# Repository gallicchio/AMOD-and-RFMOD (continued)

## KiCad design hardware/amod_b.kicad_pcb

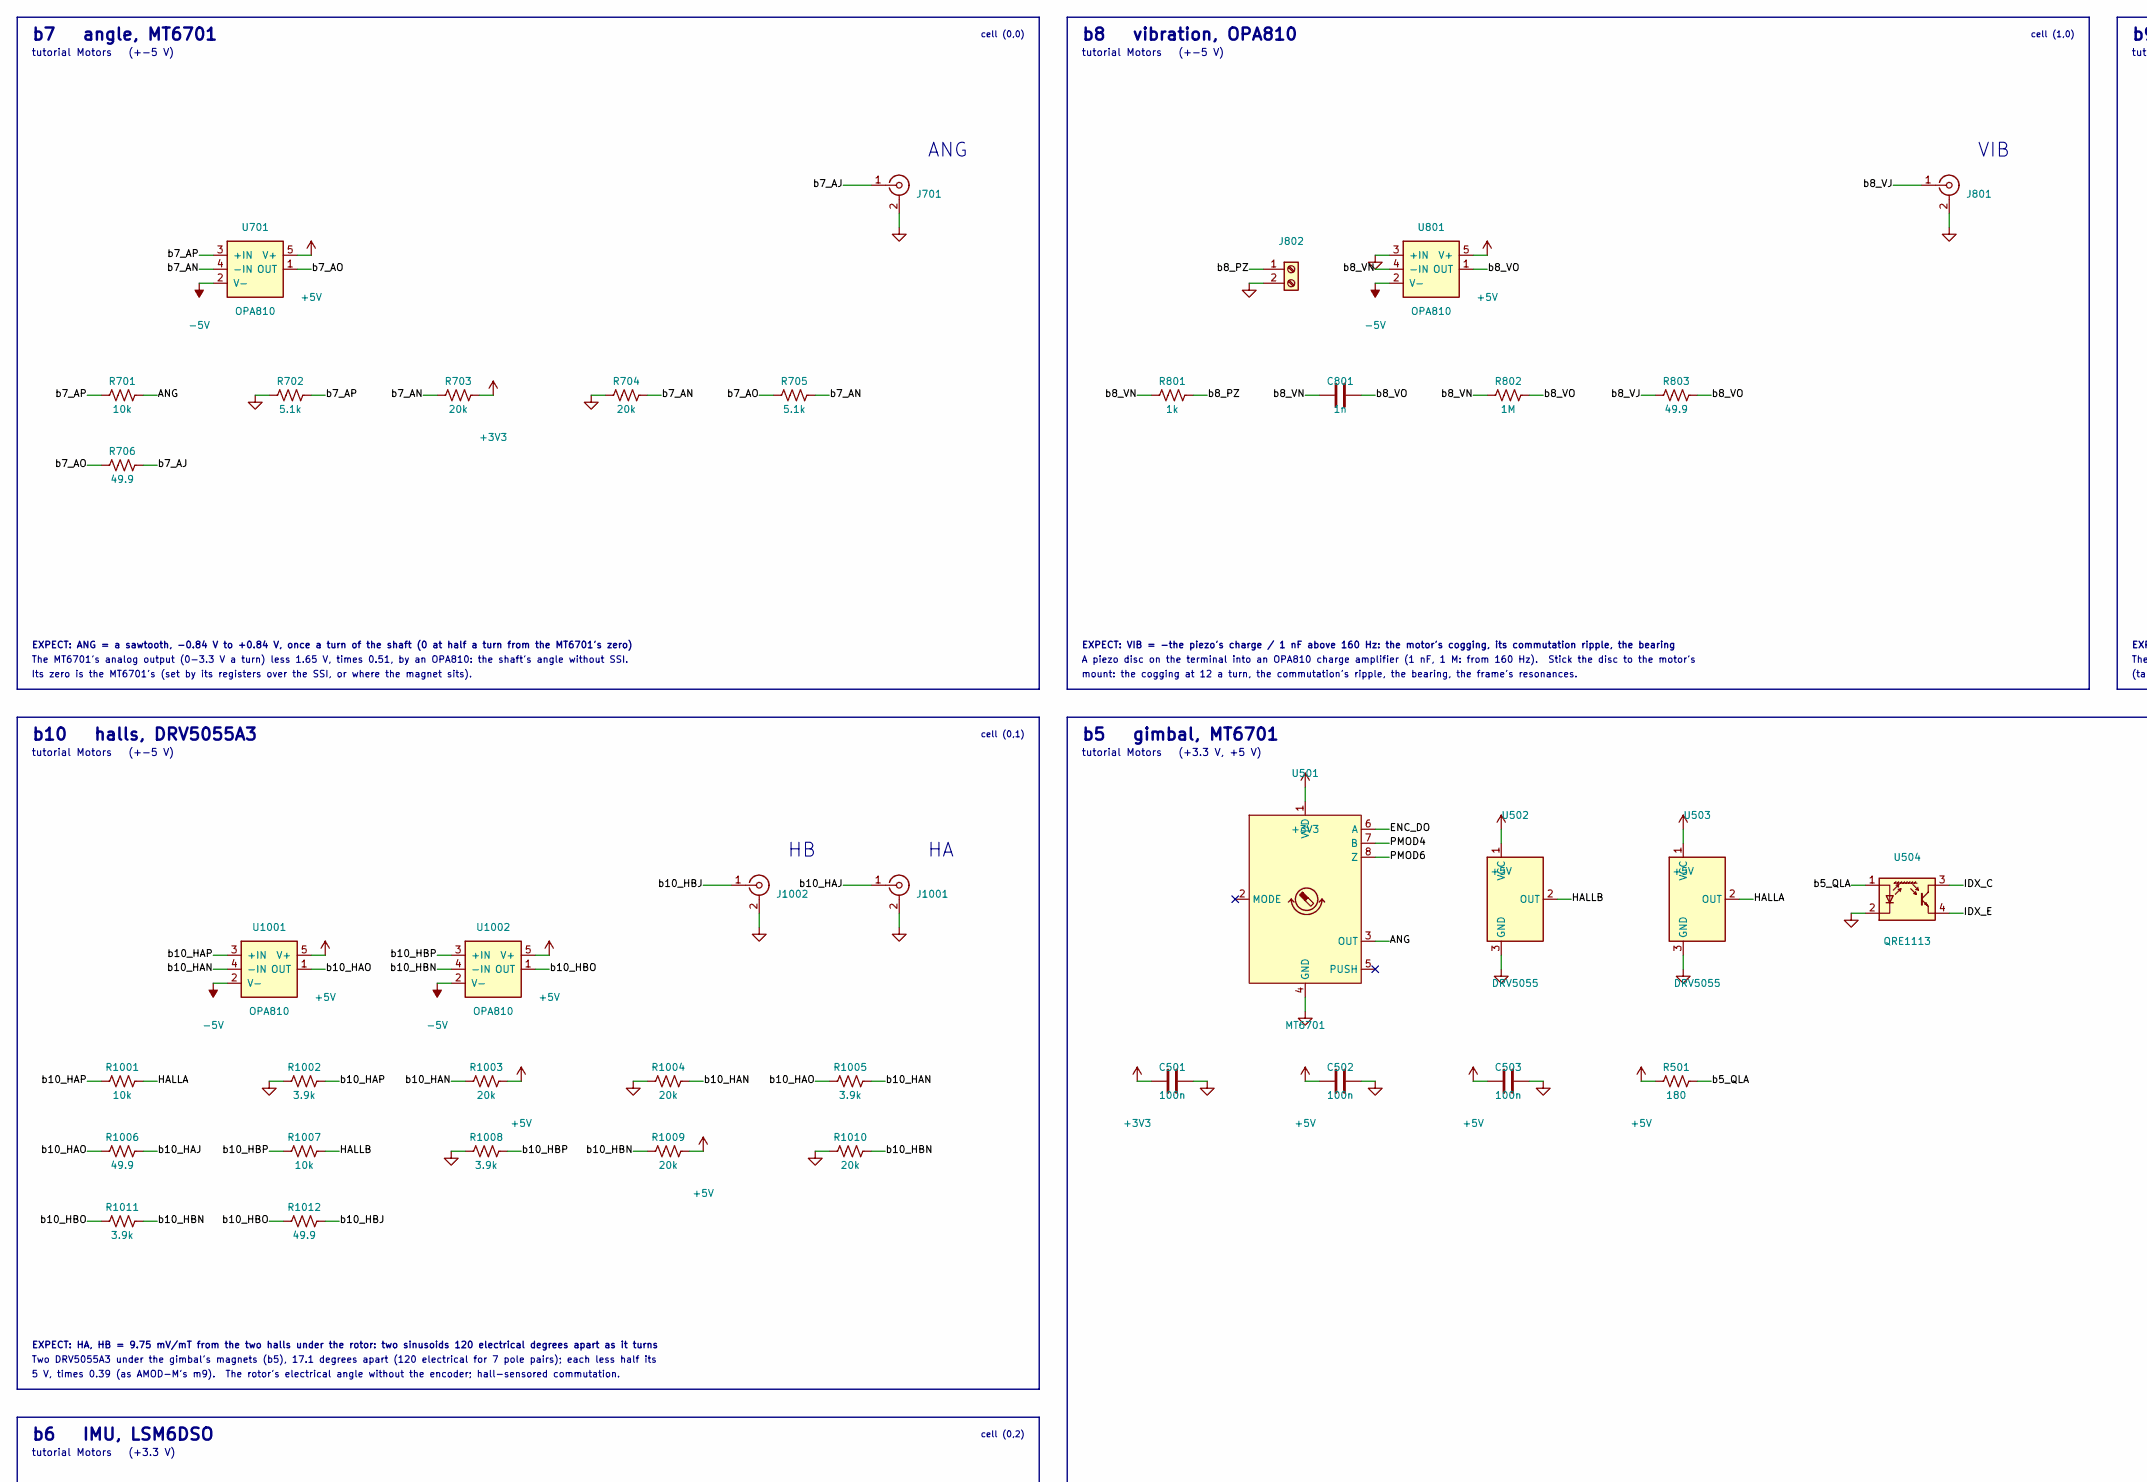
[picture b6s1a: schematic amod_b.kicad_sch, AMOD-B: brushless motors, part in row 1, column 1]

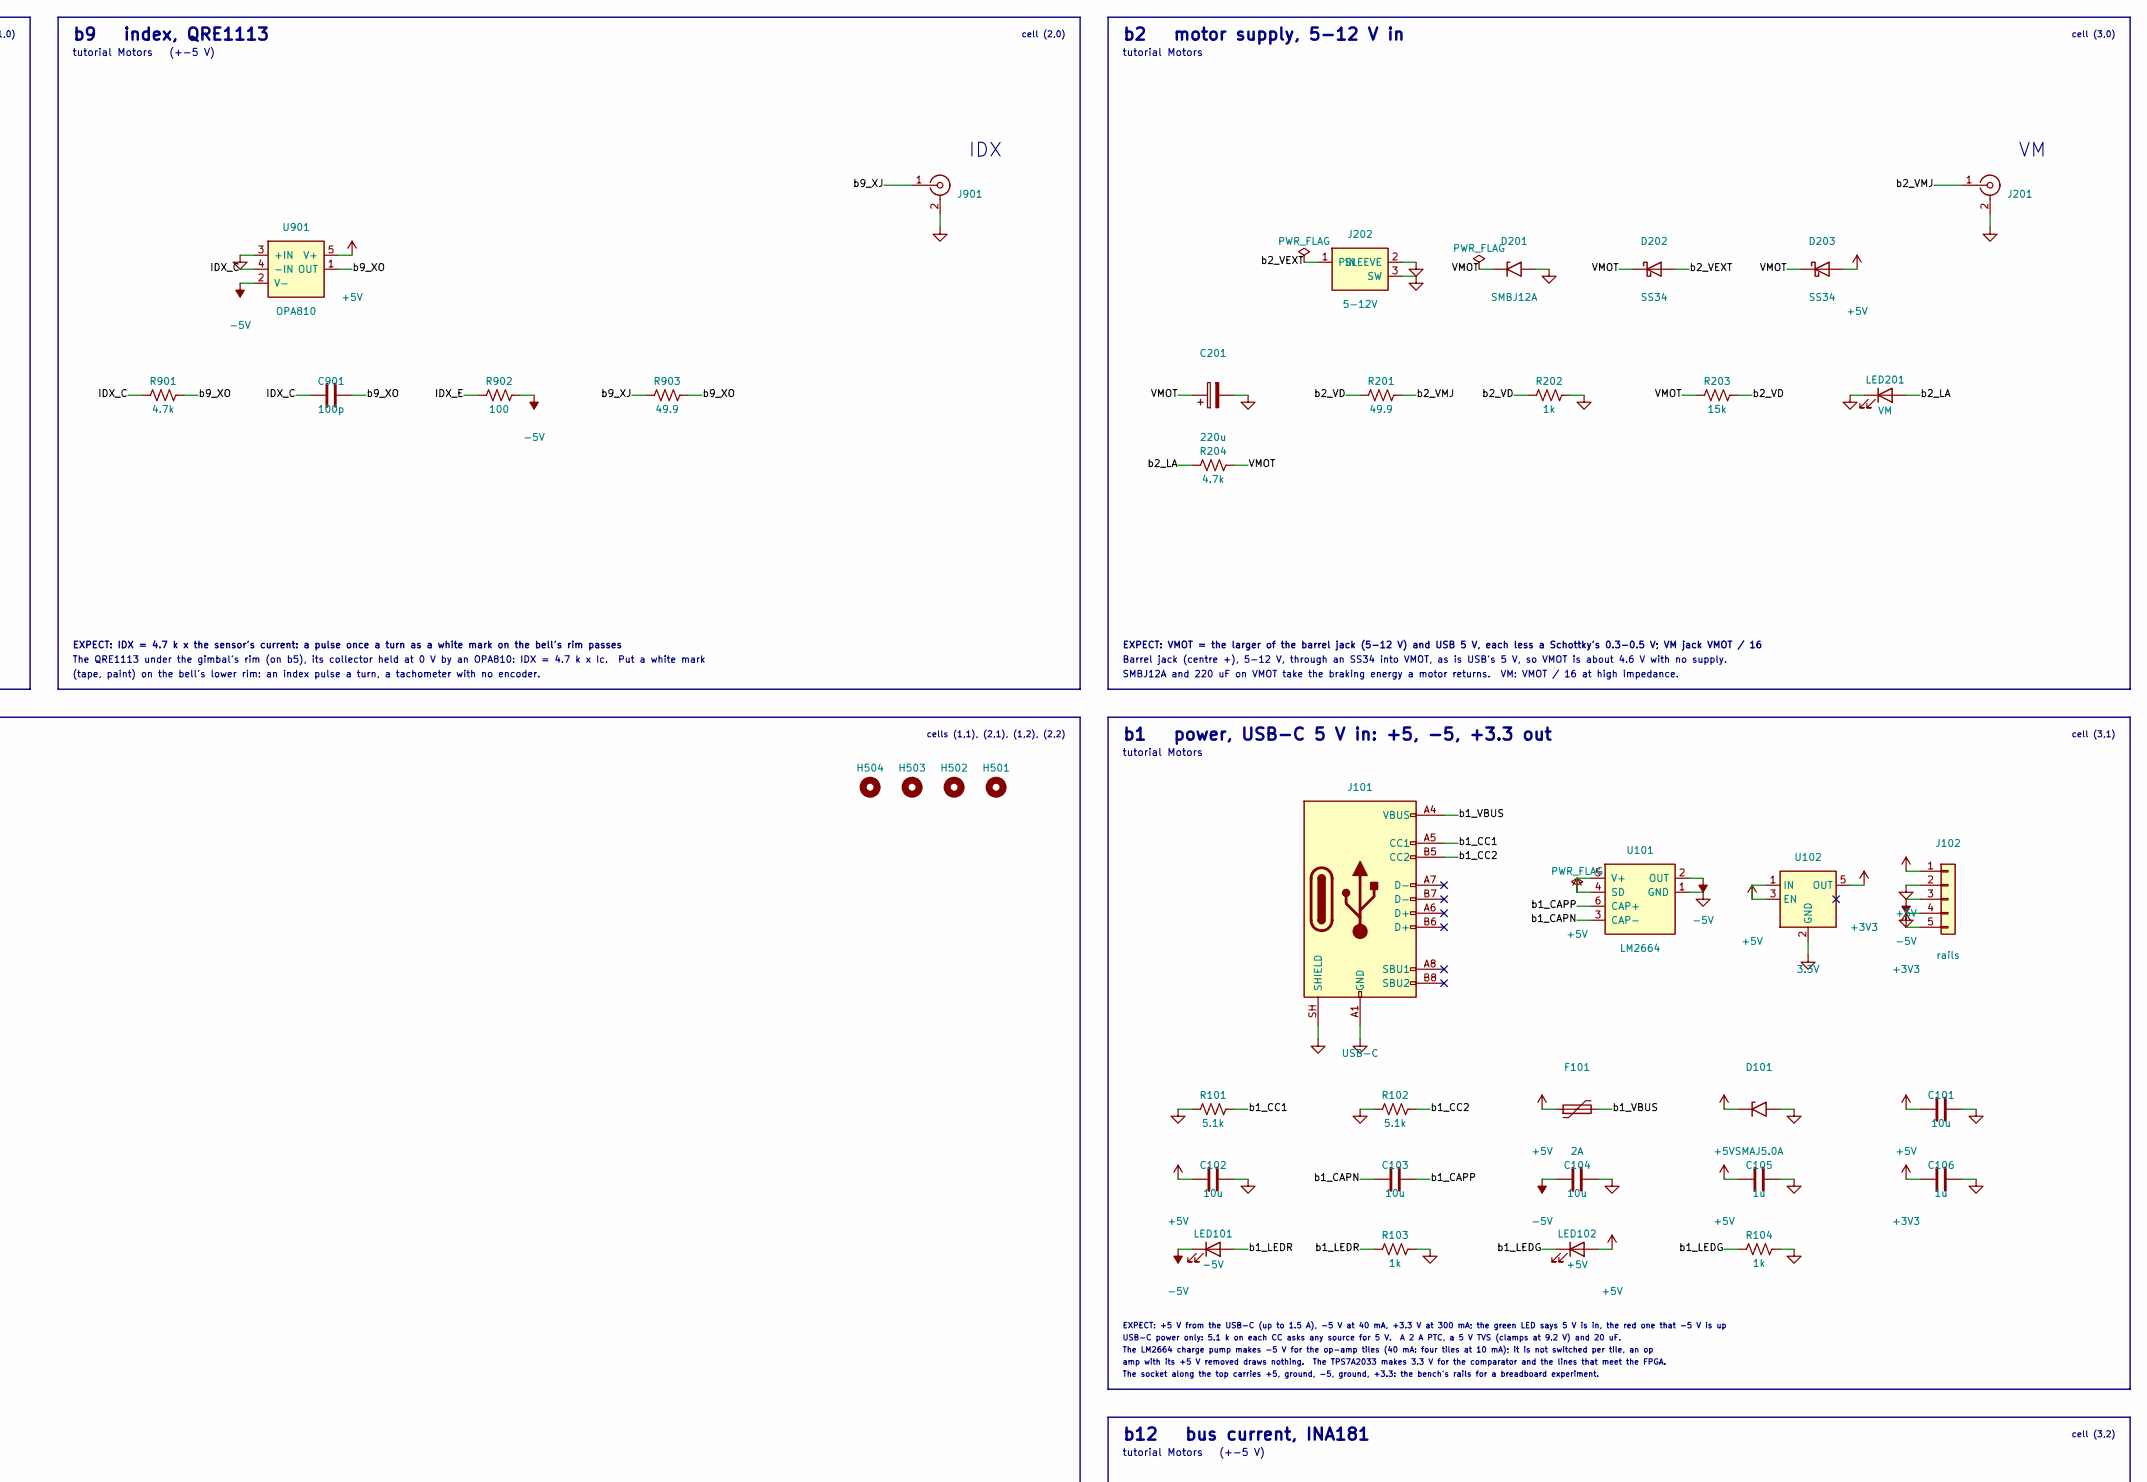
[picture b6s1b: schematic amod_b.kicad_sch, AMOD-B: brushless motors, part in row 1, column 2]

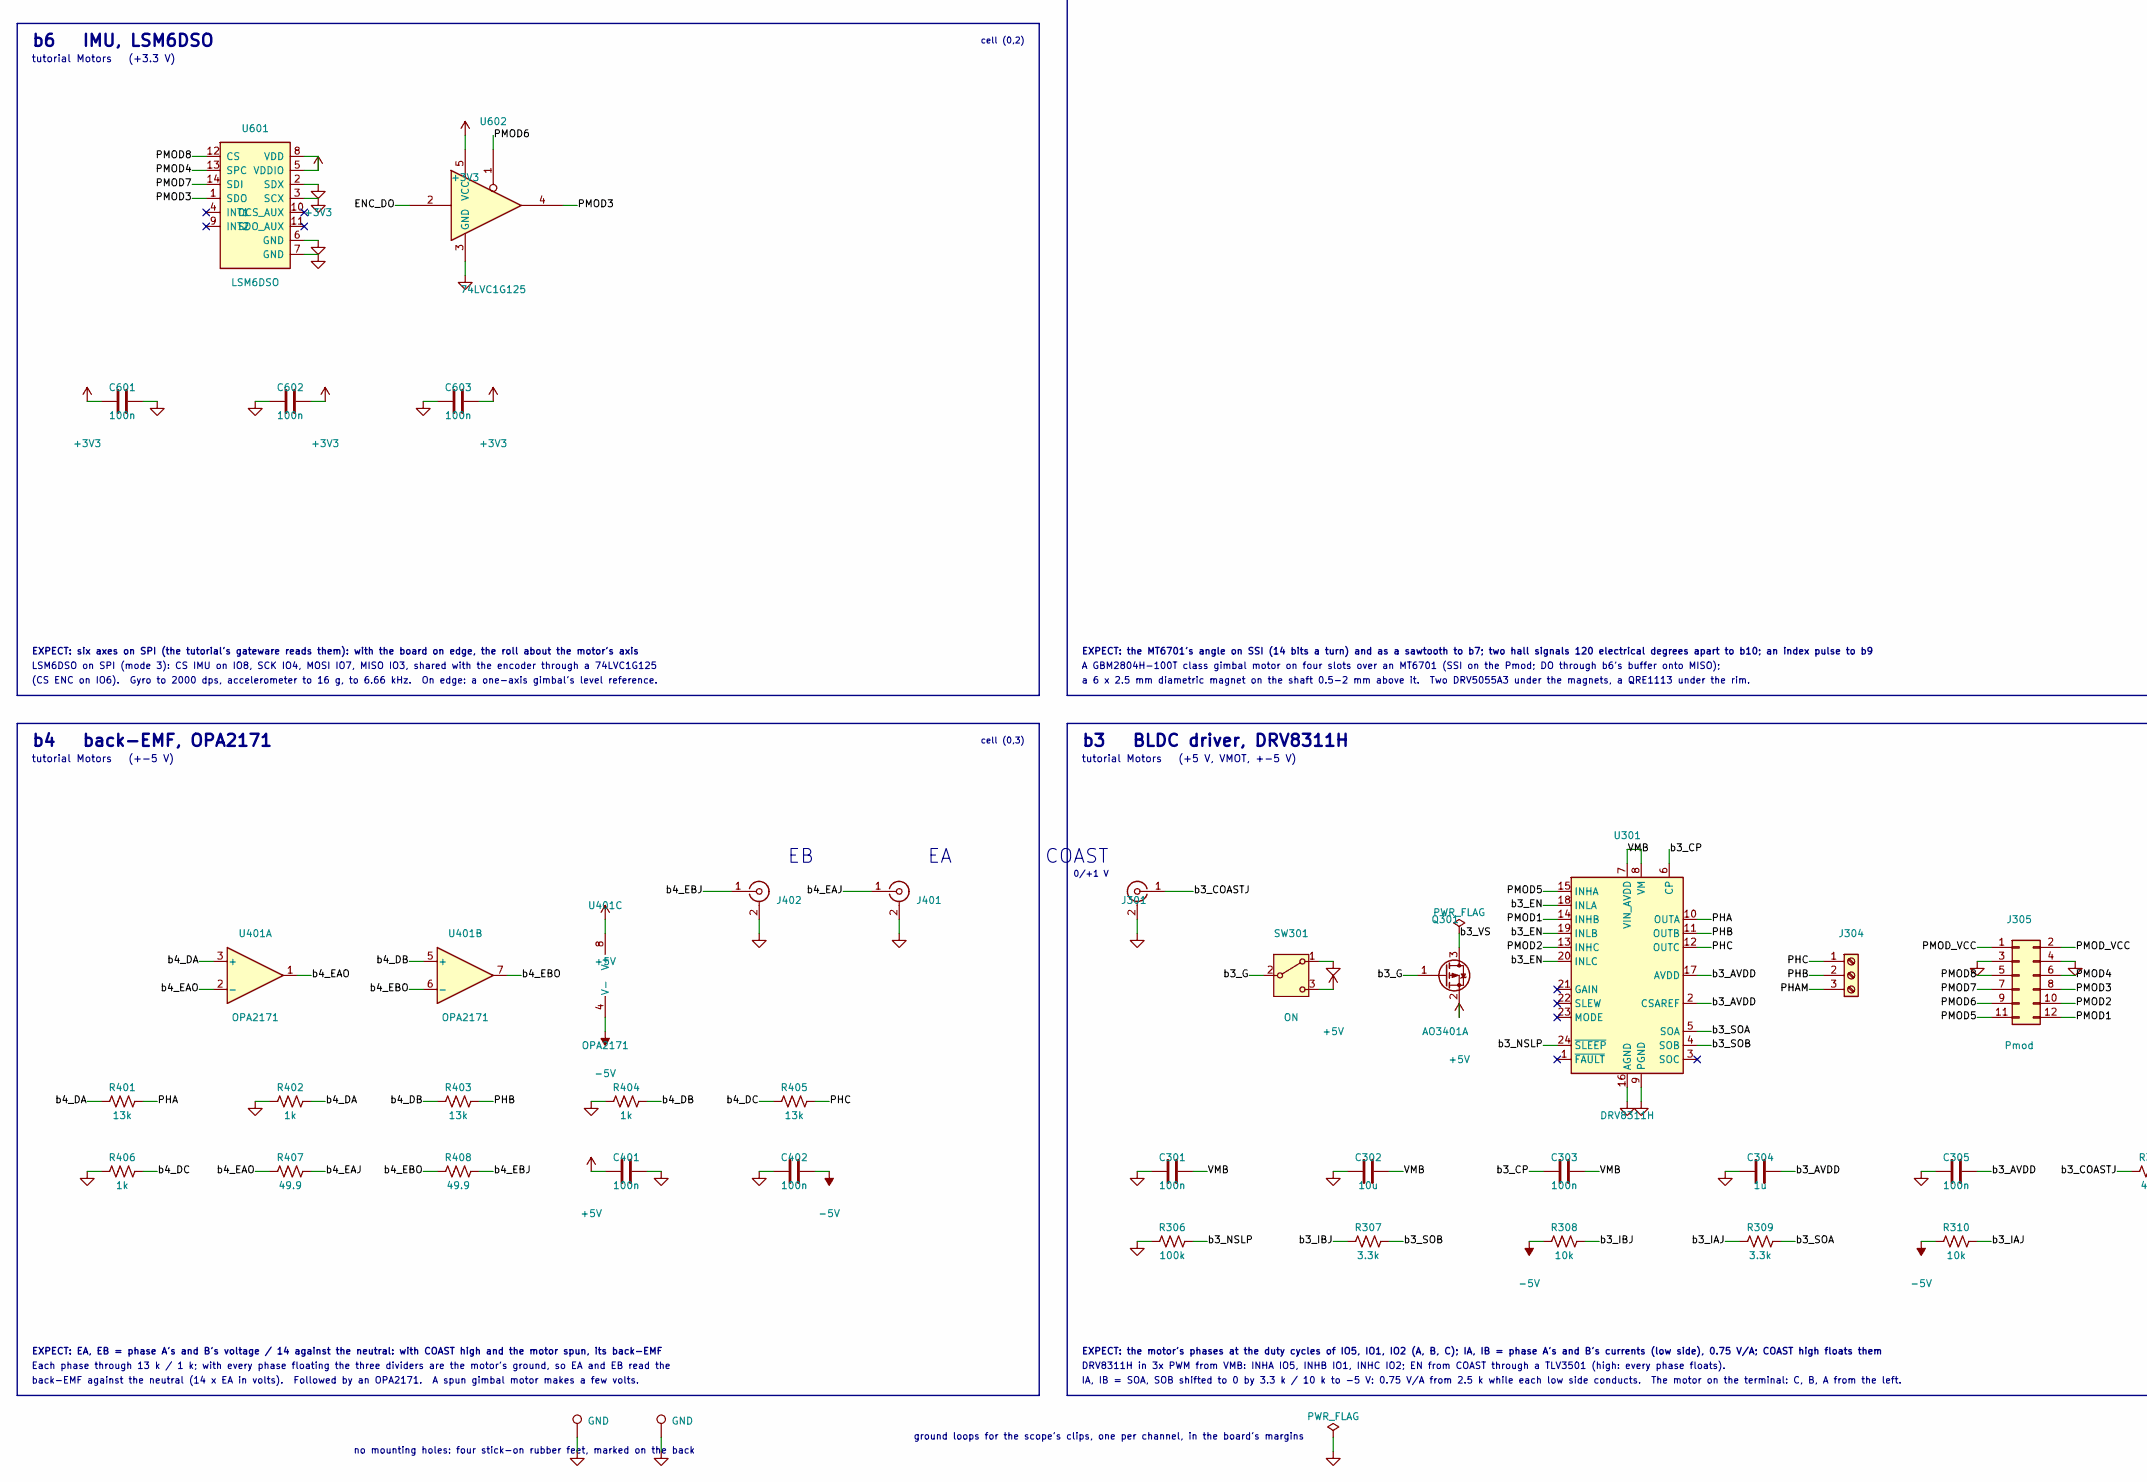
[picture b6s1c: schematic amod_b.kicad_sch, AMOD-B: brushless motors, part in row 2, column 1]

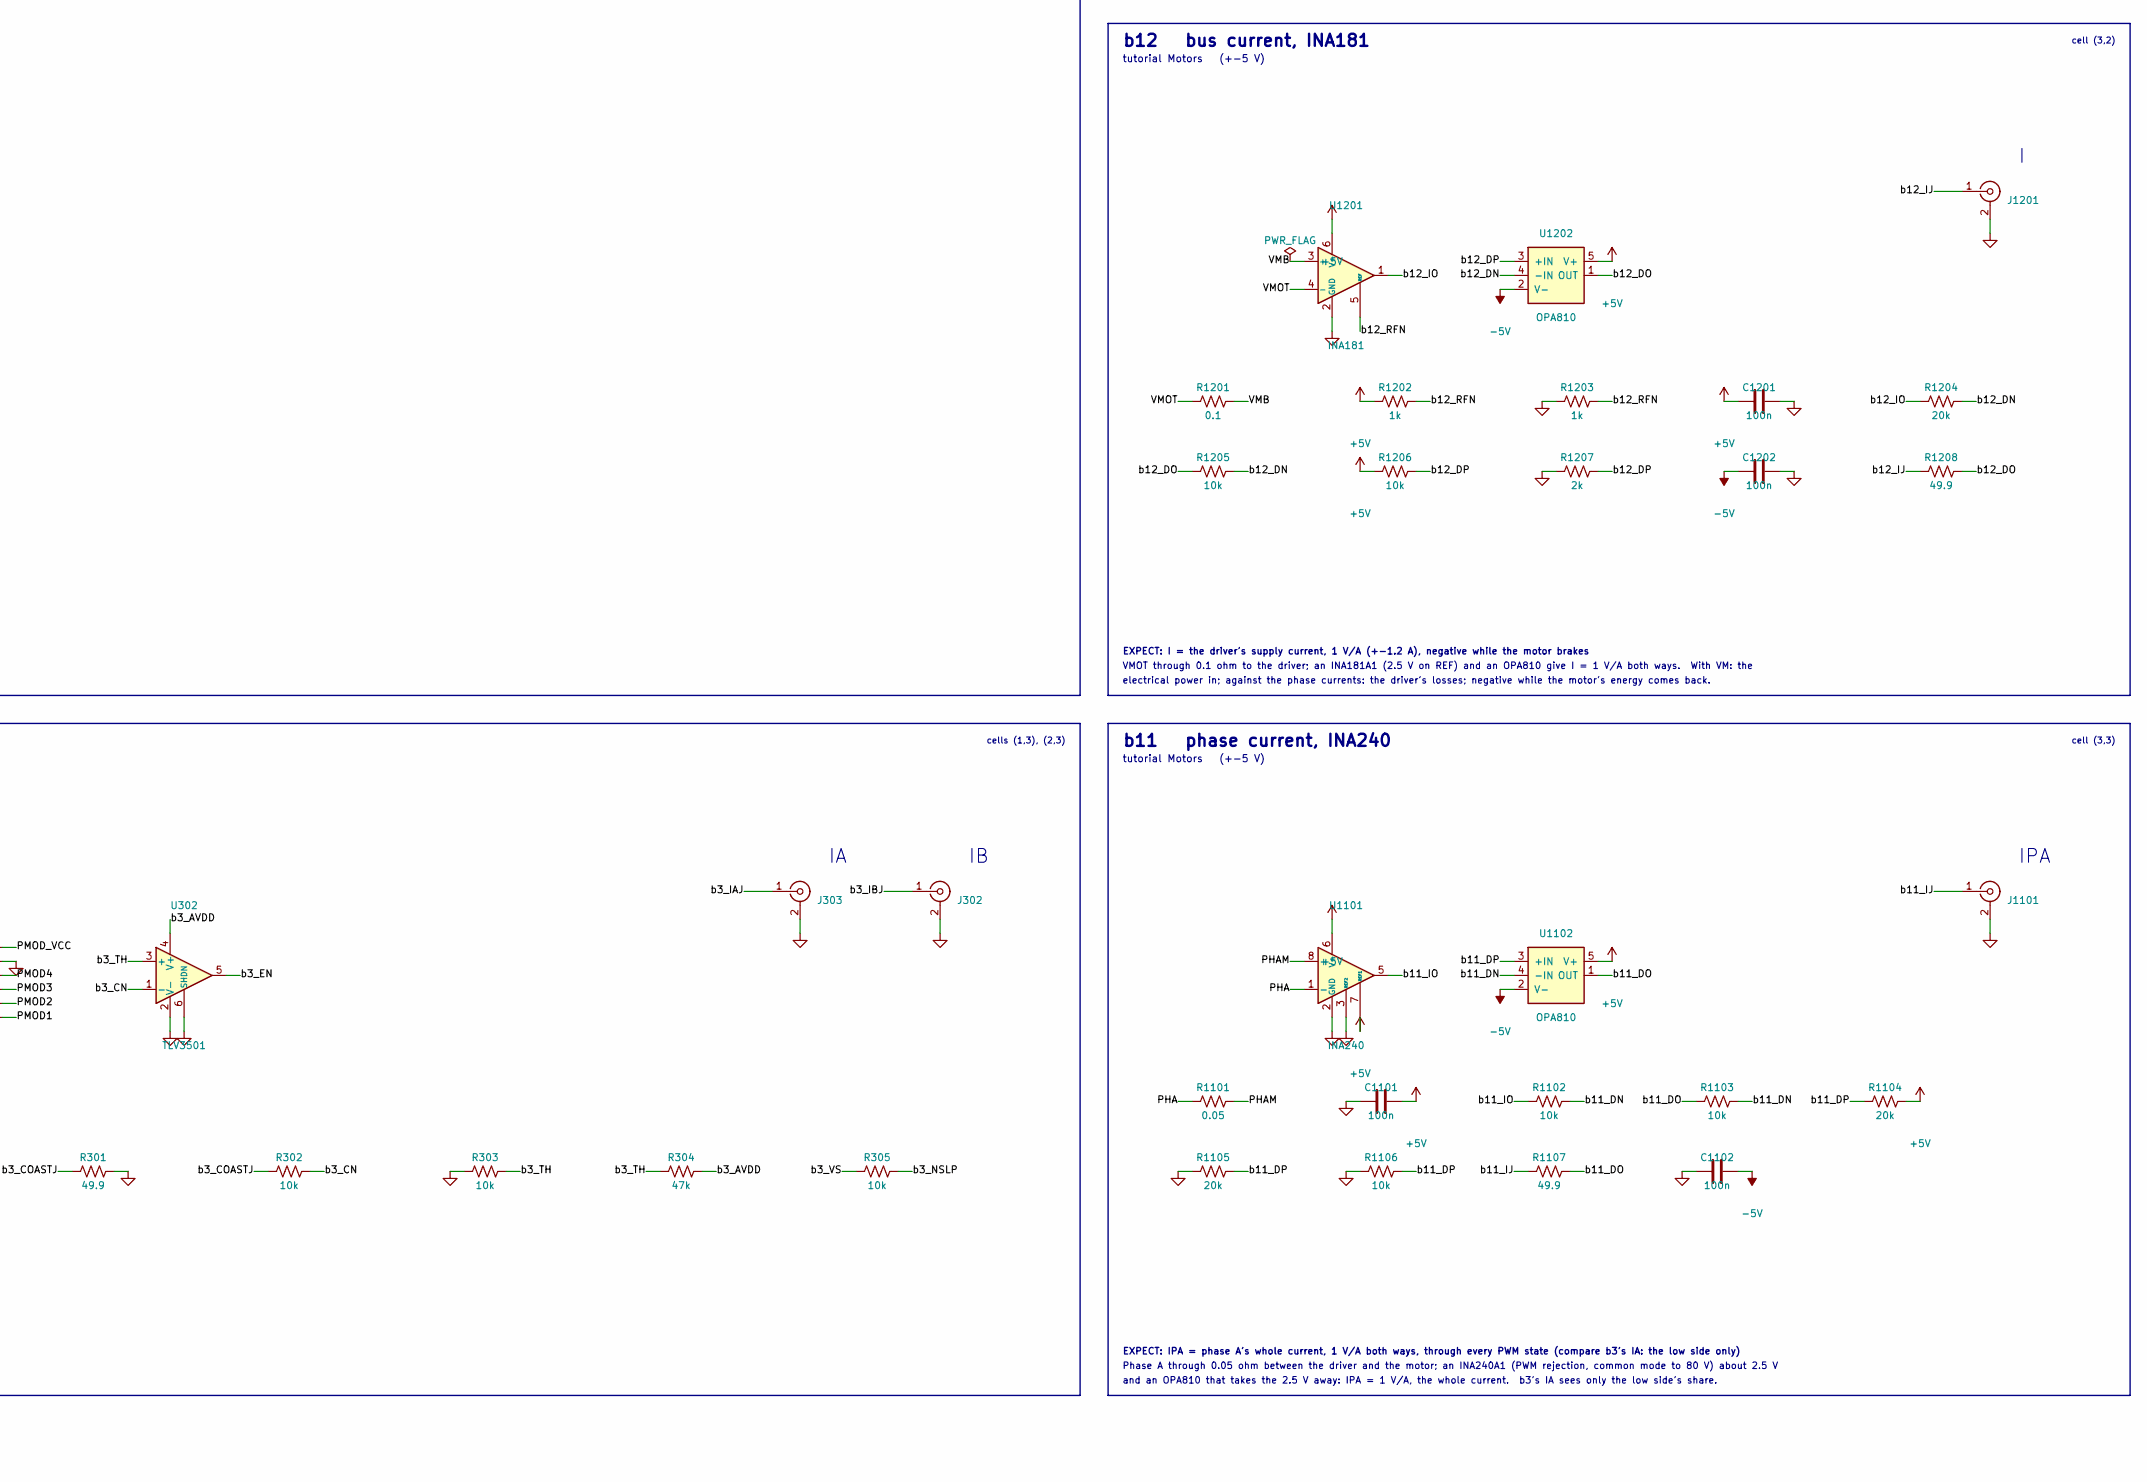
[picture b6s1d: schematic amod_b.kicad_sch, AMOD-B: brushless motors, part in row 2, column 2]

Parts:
C101, C102, C103, C104, C302: 10u; C_0805_2012Metric; MPN CL21A106KAYNNNE; LCSC C15850
C105, C106: 1u; C_0805_2012Metric; MPN CL21B105KBFNNNE; LCSC C28323
C201: 220u; CP_Elec_6.3x7.7; MPN XT220UF25V90RV0075; LCSC C2992606
C301, C303, C305, C401, C402, C501, C502, C503, C601, C602, C603, C1101, C1102, C1201, C1202: 100n; C_0402_1005Metric; MPN CL05B104KO5NNNC; LCSC C1525
C304: 1u; C_0603_1608Metric; MPN CL10A105KB8NNNC; LCSC C15849
C801: 1n; C_0402_1005Metric; MPN 0402B102K500NT; LCSC C1523
C901: 100p; C_0402_1005Metric; MPN 0402CG101J500NT; LCSC C1546
D101: SMAJ5.0A; D_SMA; MPN SMAJ5.0A; LCSC C78401
D201: SMBJ12A; D_SMB; MPN SMBJ12A; LCSC C19077565
D202, D203: SS34; D_SMA; MPN SS34; LCSC C8678
F101: 2A; Fuse_1812_4532Metric; MPN MF-MSMF200-2; LCSC C210837
H501, H502, H503, H504: slot; Slot_Motor_3.4x7.4mm
J101: USB-C; USB_C_Receptacle_HRO_TYPE-C-31-M-12; MPN TYPE-C-31-M-12; LCSC C165948
J102: rails; PinSocket_1x05_P2.54mm_Vertical; MPN PZ254-1-05-Z-8.5; LCSC C2894928
J201, J301, J302, J303, J401, J402, J701, J801, J901, J1001, J1002, J1101, J1201: SMA; SMA_BWSMA-KE-Z001_Vertical; MPN BWSMA-KE-Z001; LCSC C496549
J202: 5-12V; BarrelJack_DC-005-5A_Horizontal; MPN DC-005-5A-2.0; LCSC C381116
J304: motor; TerminalBlock_KF301_1x03_P5.00mm; MPN KF301-5.0-3P; LCSC C474882
J305: Pmod; PinHeader_2x06_P2.54mm_Horizontal_PZ254R-12-12P; MPN PZ254R-12-12P; LCSC C492434
J802: piezo; TerminalBlock_KF301_1x02_P5.00mm; MPN KF301-5.0-2P; LCSC C474881
LED101: -5V; LED_0805_2012Metric_Kbar; MPN NCD0805R1; LCSC C84256
LED102: +5V; LED_0805_2012Metric_Kbar; MPN KT-0805G; LCSC C2297
LED201: VM; LED_0805_2012Metric_Kbar; MPN KT-0805G; LCSC C2297
Q301: AO3401A; SOT-23; MPN AO3401A; LCSC C15127
R101, R102: 5.1k; R_0805_2012Metric; MPN 0805W8F5101T5E; LCSC C27834
R103, R104: 1k; R_0805_2012Metric; MPN 0805W8F1001T5E; LCSC C17513
R201, R301, R407, R408, R706, R803, R903, R1006, R1012, R1107, R1208: 49.9; R_0402_1005Metric; MPN CRCW040249R9FKEDHP; LCSC C844112
R202, R402, R404, R406, R801, R1202, R1203: 1k; R_0402_1005Metric; MPN 0402WGF1001TCE; LCSC C11702
R203: 15k; R_0402_1005Metric; MPN 0402WGF1502TCE; LCSC C25756
R204, R901: 4.7k; R_0402_1005Metric; MPN 0402WGF4701TCE; LCSC C25900
R302, R303, R305, R308, R310, R701, R1001, R1007, R1102, R1103, R1106, R1205, R1206: 10k; R_0402_1005Metric; MPN 0402WGF1002TCE; LCSC C25744
R304: 47k; R_0402_1005Metric; MPN 0402WGF4702TCE; LCSC C25792
R306: 100k; R_0402_1005Metric; MPN 0402WGF1003TCE; LCSC C25741
R307, R309: 3.3k; R_0402_1005Metric; MPN 0402WGF3301TCE; LCSC C25890
R401, R403, R405: 13k; R_0402_1005Metric; MPN 0402WGF1302TCE; LCSC C25754
R501: 180; R_0805_2012Metric; MPN 0805W8F1800T5E; LCSC C25270
R702, R705: 5.1k; R_0402_1005Metric; MPN 0402WGF5101TCE; LCSC C25905
R703, R704, R1003, R1004, R1009, R1010, R1104, R1105, R1204: 20k; R_0402_1005Metric; MPN 0402WGF2002TCE; LCSC C25765
R802: 1M; R_0805_2012Metric; MPN 0805W8F1004T5E; LCSC C17514
R902: 100; R_0402_1005Metric; MPN 0402WGF1000TCE; LCSC C25076
R1002, R1005, R1008, R1011: 3.9k; R_0402_1005Metric; MPN 0402WGF3901TCE; LCSC C51721
R1101: 0.05; R_1206_3216Metric; MPN 1206W3F500MT5E; LCSC C127691
R1201: 0.1; R_1206_3216Metric; MPN 1206W4F100LT5E; LCSC C25334
R1207: 2k; R_0402_1005Metric; MPN 0402WGF2001TCE; LCSC C4109
SW301: ON; SW_SPDT_Shouhan_MSK12C02; MPN MSK12C02; LCSC C431540
TP9901, TP9902: GND; TestPoint_Loop_RH-5019; MPN RH-5019; LCSC C5199800
U101: LM2664; SOT-23-6; MPN LM2664M6X/NOPB; LCSC C108573
U102: 3.3V; SOT-23-5; MPN TPS7A2033PDBVR; LCSC C2862740
U301: DRV8311H; Texas_RRW0024A_WQFN-24-1EP_3x3mm_P0.4mm_EP1.9x1.9mm; MPN DRV8311HRRWR; LCSC C5218862
U302: TLV3501; SOT-23-6; MPN TLV3501AIDBVR; LCSC C193413
U401: OPA2171; SOIC-8_3.9x4.9mm_P1.27mm; MPN OPA2171AIDR; LCSC C40904
U501: MT6701; SOIC-8_3.9x4.9mm_P1.27mm; MPN MT6701CT-STD-R; LCSC C3003196
U502, U503: DRV5055; SOT-23; MPN DRV5055A3QDBZR; LCSC C266128
U504: QRE1113; OnSemi_CASE100CY; MPN QRE1113GR; LCSC C232862
U601: LSM6DSO; LGA-14_3x2.5mm_P0.5mm_LayoutBorder3x4y; MPN LSM6DSOTR; LCSC C2655100
U602: 74LVC1G125; SOT-23-5; MPN SN74LVC1G125DBVR; LCSC C23654
U701, U801, U901, U1001, U1002, U1102, U1202: OPA810; SOT-23-5; MPN OPA810IDBVR; LCSC C2833513
U1101: INA240; SOIC-8_3.9x4.9mm_P1.27mm; MPN INA240A1DR; LCSC C2060769
U1201: INA181; SOT-23-6; MPN INA181A1IDBVR; LCSC C2058943

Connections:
+3V3: C106.1, C501.1, C601.1, C602.2, C603.2, J102.5, R703.2, U102.5 (OUT), U501.1 (VDD), U601.5 (VDDIO), U601.8 (VDD), U602.5 (VCC)
+5V: C101.1, C102.1, C105.1, C401.1, C502.1, C503.1, C1101.2, C1201.1, D101.1 (A1), D203.2 (A), F101.1, J102.1, LED102.2 (A), Q301.2 (S), R501.1, R1003.2, R1009.2, R1104.2, R1202.1, R1206.1, SW301.3 (C), U101.4 (SD), U101.5 (V+), U102.1 (IN), U102.3 (EN), U401.8 (V+), U502.1 (VCC), U503.1 (VCC), U701.5 (V+), U801.5 (V+), U901.5 (V+), U1001.5 (V+), U1002.5 (V+), U1101.6 (V+), U1101.7 (REF1), U1102.5 (V+), U1201.6 (V+), U1202.5 (V+)
-5V: C104.1, C402.2, C1102.2, C1202.1, J102.3, LED101.1 (K), R308.1, R310.1, R902.2, U101.2 (OUT), U401.4 (V-), U701.2 (V-), U801.2 (V-), U901.2 (V-), U1001.2 (V-), U1002.2 (V-), U1102.2 (V-), U1202.2 (V-)
/ANG: R701.2, U501.3 (OUT)
/ENC_DO: U501.6 (A), U602.2
/HALLA: R1001.2, U503.2 (OUT)
/HALLB: R1007.2, U502.2 (OUT)
/IDX_C: C901.1, R901.1, U504.3, U901.4 (-IN)
/IDX_E: R902.1, U504.4
/PHA: R401.2, R1101.1, U301.10 (OUTA), U1101.1 (-)
/PHAM: J304.3, R1101.2, U1101.8 (+)
/PHB: J304.2, R403.2, U301.11 (OUTB)
/PHC: J304.1, R405.2, U301.12 (OUTC)
/PMOD1: J305.12, U301.14 (INHB)
/PMOD2: J305.10, U301.13 (INHC)
/PMOD3: J305.8, U601.1 (SDO), U602.4
/PMOD4: J305.6, U501.7 (B), U601.13 (SPC)
/PMOD5: J305.11, U301.15 (INHA)
/PMOD6: J305.9, U501.8 (Z), U602.1
/PMOD7: J305.7, U601.14 (SDI)
/PMOD8: J305.5, U601.12 (CS)
/PMOD_VCC: J305.1, J305.2
/VMB: C301.2, C302.2, C303.2, R1201.2, U301.7 (VIN_AVDD), U301.8 (VM), U1201.3 (+)
/VMOT: C201.1, D201.1 (A1), D202.1 (K), D203.1 (K), R203.1, R204.2, R1201.1, U1201.4 (-)
/b1_CAPN: C103.1, U101.3 (CAP-)
/b1_CAPP: C103.2, U101.6 (CAP+)
/b1_CC1: J101.A5 (CC1), R101.2
/b1_CC2: J101.B5 (CC2), R102.2
/b1_LEDG: LED102.1 (K), R104.1
/b1_LEDR: LED101.2 (A), R103.1
/b1_VBUS: F101.2, J101.A4 (VBUS), J101.A9 (VBUS), J101.B4 (VBUS), J101.B9 (VBUS)
/b2_LA: LED201.2 (A), R204.1
/b2_VD: R201.1, R202.1, R203.2
/b2_VEXT: D202.2 (A), J202.1 (PIN)
/b2_VMJ: J201.1 (In), R201.2
/b3_AVDD: C304.2, C305.2, R304.2, U301.2 (CSAREF), U301.17 (AVDD), U302.4 (V+)
/b3_CN: R302.2, U302.1 (-)
/b3_COASTJ: J301.1 (In), R301.1, R302.1
/b3_CP: C303.1, U301.6 (CP)
/b3_EN: U301.18 (INLA), U301.19 (INLB), U301.20 (INLC), U302.5
/b3_G: Q301.1 (G), SW301.2 (B)
/b3_IAJ: J303.1 (In), R309.1, R310.2
/b3_IBJ: J302.1 (In), R307.1, R308.2
/b3_NSLP: R305.2, R306.2, U301.24 (~SLEEP)
/b3_SOA: R309.2, U301.5 (SOA)
/b3_SOB: R307.2, U301.4 (SOB)
/b3_TH: R303.2, R304.1, U302.3 (+)
/b3_VS: Q301.3 (D), R305.1
/b4_DA: R401.1, R402.2, U401.3 (+)
/b4_DB: R403.1, R404.2, U401.5 (+)
/b4_DC: R405.1, R406.2
/b4_EAJ: J401.1 (In), R407.2
/b4_EAO: R407.1, U401.1, U401.2 (-)
/b4_EBJ: J402.1 (In), R408.2
/b4_EBO: R408.1, U401.6 (-), U401.7
/b5_QLA: R501.2, U504.1 (A)
/b7_AJ: J701.1 (In), R706.2
/b7_AN: R703.1, R704.2, R705.2, U701.4 (-IN)
/b7_AO: R705.1, R706.1, U701.1 (OUT)
/b7_AP: R701.1, R702.2, U701.3 (+IN)
/b8_PZ: J802.1, R801.2
/b8_VJ: J801.1 (In), R803.1
/b8_VN: C801.1, R801.1, R802.1, U801.4 (-IN)
/b8_VO: C801.2, R802.2, R803.2, U801.1 (OUT)
/b9_XJ: J901.1 (In), R903.1
/b9_XO: C901.2, R901.2, R903.2, U901.1 (OUT)
/b10_HAJ: J1001.1 (In), R1006.2
/b10_HAN: R1003.1, R1004.2, R1005.2, U1001.4 (-IN)
/b10_HAO: R1005.1, R1006.1, U1001.1 (OUT)
/b10_HAP: R1001.1, R1002.2, U1001.3 (+IN)
/b10_HBJ: J1002.1 (In), R1012.2
/b10_HBN: R1009.1, R1010.2, R1011.2, U1002.4 (-IN)
/b10_HBO: R1011.1, R1012.1, U1002.1 (OUT)
/b10_HBP: R1007.1, R1008.2, U1002.3 (+IN)
/b11_DN: R1102.2, R1103.2, U1102.4 (-IN)
/b11_DO: R1103.1, R1107.2, U1102.1 (OUT)
/b11_DP: R1104.1, R1105.2, R1106.2, U1102.3 (+IN)
/b11_IJ: J1101.1 (In), R1107.1
/b11_IO: R1102.1, U1101.5
/b12_DN: R1204.2, R1205.2, U1202.4 (-IN)
/b12_DO: R1205.1, R1208.2, U1202.1 (OUT)
/b12_DP: R1206.2, R1207.2, U1202.3 (+IN)
/b12_IJ: J1201.1 (In), R1208.1
/b12_IO: R1204.1, U1201.1
/b12_RFN: R1202.2, R1203.2, U1201.5 (REF)
GND: C101.2, C102.2, C104.2, C105.2, C106.2, C201.2, C301.1, C302.1, C304.1, C305.1, C401.2, C402.1, C501.2, C502.2, C503.2, C601.2, C602.1, C603.1, C1101.1, C1102.1, C1201.2, C1202.2, D101.2 (A2), D201.2 (A2), J101.A1 (GND), J101.A12 (GND), J101.B1 (GND), J101.B12 (GND), J101.SH (SHIELD), J102.2, J102.4, J201.2 (Ext), J202.2 (SLEEVE), J202.3 (SW), J301.2 (Ext), J302.2 (Ext), J303.2 (Ext), J305.3, J305.4, J401.2 (Ext), J402.2 (Ext), J701.2 (Ext), J801.2 (Ext), J802.2, J901.2 (Ext), J1001.2 (Ext), J1002.2 (Ext), J1101.2 (Ext), J1201.2 (Ext), LED201.1 (K), R101.1, R102.1, R103.2, R104.2, R202.2, R301.2, R303.1, R306.1, R402.1, R404.1, R406.1, R702.1, R704.1, R1002.1, R1004.1, R1008.1, R1010.1, R1105.1, R1106.1, R1203.1, R1207.1, SW301.1 (A), TP9901.1, TP9902.1, U101.1 (GND), U102.2 (GND), U301.9 (PGND), U301.16 (AGND), U301.25 (PGND), U302.2 (V-), U302.6 (SHDN), U501.4 (GND), U502.3 (GND), U503.3 (GND), U504.2 (K), U601.2 (SDX), U601.3 (SCX), U601.6 (GND), U601.7 (GND), U602.3 (GND), U801.3 (+IN), U901.3 (+IN), U1101.2 (GND), U1101.3 (REF2), U1101.4 (GND), U1201.2 (GND)

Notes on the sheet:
The MT6701's analog output (0-3.3 V a turn) less 1.65 V, times 0.51, by an OPA810: the shaft's angle without SSI.
tutorial Motors (+5 V, VMOT, +-5 V)
electrical power in; against the phase currents: the driver's losses; negative while the motor's energy comes back.
(tape, paint) on the bell's lower rim: an index pulse a turn, a tachometer with no encoder.
b2 motor supply, 5-12 V in
tutorial Motors (+-5 V)
cell (0,2)
cell (2,0)
The QRE1113 under the gimbal's rim (on b5), its collector held at 0 V by an OPA810: IDX = 4.7 k x Ic. Put a white mark
cell (3,3)
cells (1,3), (2,3)
USB-C power only: 5.1 k on each CC asks any source for 5 V. A 2 A PTC, a 5 V TVS (clamps at 9.2 V) and 20 uF.
LSM6DSO on SPI (mode 3): CS IMU on IO8, SCK IO4, MOSI IO7, MISO IO3, shared with the encoder through a 74LVC1G125
b12 bus current, INA181
The socket along the top carries +5, ground, -5, ground, +3.3: the bench's rails for a breadboard experiment.
0/+1 V
tutorial Motors (+3.3 V)
cell (0,1)
tutorial Motors
VMOT through 0.1 ohm to the driver; an INA181A1 (2.5 V on REF) and an OPA810 give I = 1 V/A both ways. With VM: the
cell (0,3)
IDX
amp with its +5 V removed draws nothing. The TPS7A2033 makes 3.3 V for the comparator and the lines that meet the FPGA.
a 6 x 2.5 mm diametric magnet on the shaft 0.5-2 mm above it. Two DRV5055A3 under the magnets, a QRE1113 under the rim.
SMBJ12A and 220 uF on VMOT take the braking energy a motor returns. VM: VMOT / 16 at high impedance.
The LM2664 charge pump makes -5 V for the op-amp tiles (40 mA: four tiles at 10 mA); it is not switched per tile, an op
back-EMF against the neutral (14 x EA in volts). Followed by an OPA2171. A spun gimbal motor makes a few volts.
IA, IB = SOA, SOB shifted to 0 by 3.3 k / 10 k to -5 V: 0.75 V/A from 2.5 k while each low side conducts. The motor on the terminal: C, B, A from the left.
cells (1,1), (2,1), (1,2), (2,2)
ground loops for the scope's clips, one per channel, in the board's margins
no mounting holes: four stick-on rubber feet, marked on the back
b11 phase current, INA240
5 V, times 0.39 (as AMOD-M's m9). The rotor's electrical angle without the encoder; hall-sensored commutation.
Each phase through 13 k / 1 k; with every phase floating the three dividers are the motor's ground, so EA and EB read the
COAST
and an OPA810 that takes the 2.5 V away: IPA = 1 V/A, the whole current. b3's IA sees only the low side's share.
EXPECT: VMOT = the larger of the barrel jack (5-12 V) and USB 5 V, each less a Schottky's 0.3-0.5 V; VM jack VMOT / 16
EXPECT: the MT6701's angle on SSI (14 bits a turn) and as a sawtooth to b7; two hall signals 120 electrical degrees apart to b10; an index pulse to b9
b4 back-EMF, OPA2171
Barrel jack (centre +), 5-12 V, through an SS34 into VMOT, as is USB's 5 V, so VMOT is about 4.6 V with no supply.
